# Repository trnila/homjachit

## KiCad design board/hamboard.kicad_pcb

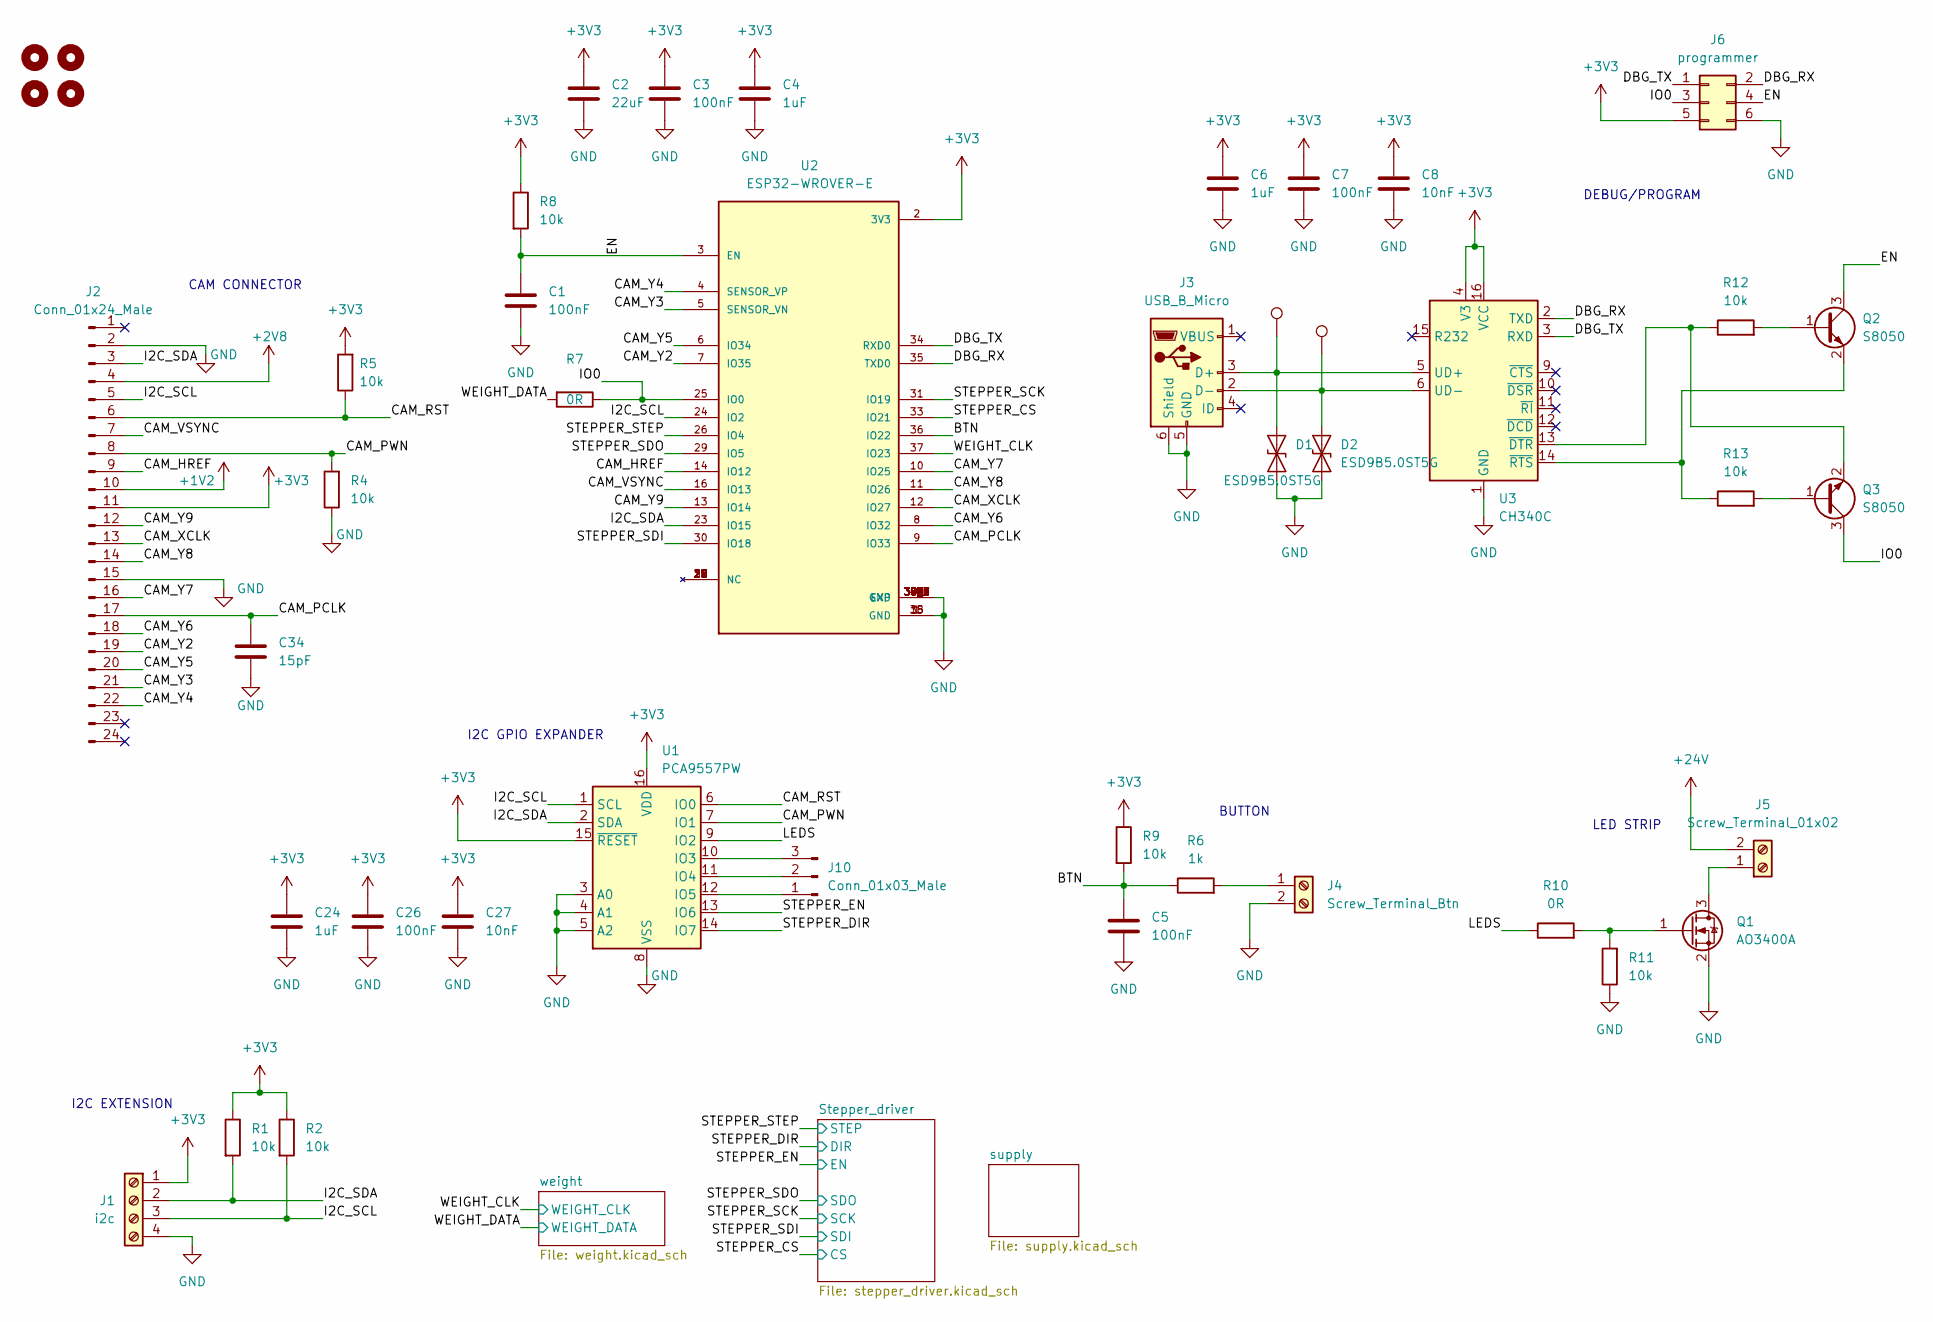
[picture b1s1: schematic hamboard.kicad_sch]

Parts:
C1, C3, C5, C7, C26: 100nF; C_0805_2012Metric; LCSC C282732
C2: 22uF; CP_EIA-1608-10_AVX-L; LCSC C29277
C4, C6, C24: 1uF; C_0805_2012Metric; LCSC C2798196
C8, C27: 10nF; C_0805_2012Metric; LCSC C376921
C34: 15pF; C_0805_2012Metric; LCSC C63339
D1, D2: ESD9B5.0ST5G; D_SOD-923; LCSC C2985641
H1, H2, H3, H4: MountingHole; MountingHole_3.2mm_M3
J1: i2c; PinHeader_1x04_P2.54mm_Vertical; LCSC C557656
J2: Conn_01x24_Male; Hirose_FH12-24S-0.5SH_1x24-1MP_P0.50mm_Horizontal; LCSC C2858298
J3: USB_B_Micro; USB_Micro-B_GCT_USB3076-30-A; LCSC C132562
J4: Screw_Terminal_Btn; TerminalBlock_bornier-2_P5.08mm; LCSC C394556
J5: Screw_Terminal_01x02; TerminalBlock_bornier-2_P5.08mm; LCSC C394556
J6: programmer; PinHeader_2x03_P2.54mm_Vertical
J10: Conn_01x03_Male; PinHeader_1x03_P2.54mm_Vertical
Q1: AO3400A; SOT-23; LCSC C347475
Q2, Q3: S8050; SOT-23; LCSC C2891804
R1, R2, R4, R5, R8, R9, R11, R12, R13: 10k; R_0805_2012Metric; LCSC C2930231
R6: 1k; R_0805_2012Metric; LCSC C2907295
R7: 0R; R_0805_2012Metric; LCSC C2930231
R10: 0R; R_0805_2012Metric; LCSC C2907288
TP10, TP11: TestPoint; TestPoint_Pad_D1.5mm
U1: PCA9557PW; TSSOP-16_4.4x5mm_P0.65mm; LCSC C141380
U2: ESP32-WROVER-E; XCVR_ESP32-WROVER-E-N4R8; PARTREV 1.6; LCSC C529589
U3: CH340C; SOIC-16_3.9x9.9mm_P1.27mm; LCSC C84681

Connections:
+1V2: J2.10; also elsewhere on the board
+2V8: J2.4; also elsewhere on the board
+3V3: C2.1, C3.1, C4.1, C6.1, C7.1, C8.1, C24.1, C26.1, C27.1, J1.1, J2.11, J6.5, R1.1, R2.1, R5.2, R8.1, R9.1, U1.15 (~RESET), U1.16 (VDD), U2.2 (3V3), U3.4 (V3), U3.16 (VCC); also elsewhere on the board
+24V: J5.2; also elsewhere on the board
/BTN: C5.1, R6.1, R9.2, U2.36 (IO22)
/CAM_HREF: J2.9, U2.14 (IO12)
/CAM_PCLK: C34.1, J2.17, U2.9 (IO33)
/CAM_PWN: J2.8, R4.2, U1.7 (IO1)
/CAM_RST: J2.6, R5.1, U1.6 (IO0)
/CAM_VSYNC: J2.7, U2.16 (IO13)
/CAM_XCLK: J2.13, U2.12 (IO27)
/CAM_Y2: J2.19, U2.7 (IO35)
/CAM_Y3: J2.21, U2.5 (SENSOR_VN)
/CAM_Y4: J2.22, U2.4 (SENSOR_VP)
/CAM_Y5: J2.20, U2.6 (IO34)
/CAM_Y6: J2.18, U2.8 (IO32)
/CAM_Y7: J2.16, U2.10 (IO25)
/CAM_Y8: J2.14, U2.11 (IO26)
/CAM_Y9: J2.12, U2.13 (IO14)
/DBG_RX: J6.2, U2.35 (TXD0), U3.2 (TXD)
/DBG_TX: J6.1, U2.34 (RXD0), U3.3 (RXD)
/EN: C1.1, J6.4, Q2.3 (C), R8.2, U2.3 (EN)
/I2C_SCL: J1.3, J2.5, R2.2, U1.1 (SCL), U2.24 (IO2)
/I2C_SDA: J1.2, J2.3, R1.2, U1.2 (SDA), U2.23 (IO15)
/IO0: J6.3, Q3.3 (C), R7.1, U2.25 (IO0)
/LEDS: R10.1, U1.9 (IO2)
/STEPPER_CS: U2.33 (IO21); also elsewhere on the board
/STEPPER_DIR: U1.14 (IO7); also elsewhere on the board
/STEPPER_EN: U1.13 (IO6); also elsewhere on the board
/STEPPER_SCK: U2.31 (IO19); also elsewhere on the board
/STEPPER_SDI: U2.30 (IO18); also elsewhere on the board
/STEPPER_SDO: U2.29 (IO5); also elsewhere on the board
/STEPPER_STEP: U2.26 (IO4); also elsewhere on the board
/WEIGHT_CLK: U2.37 (IO23); also elsewhere on the board
/WEIGHT_DATA: R7.2; also elsewhere on the board
GND: C1.2, C2.2, C3.2, C4.2, C5.2, C6.2, C7.2, C8.2, C24.2, C26.2, C27.2, C34.2, D1.1 (A1), D2.1 (A1), J1.4, J2.2, J2.15, J3.5 (GND), J3.6 (Shield), J4.2, J6.6, Q1.2 (S), R4.1, R11.1, U1.3 (A0), U1.4 (A1), U1.5 (A2), U1.8 (VSS), U2.1 (GND), U2.15 (GND), U2.38 (GND), U2.39_1 (EXP), U2.39_2 (EXP), U2.39_3 (EXP), U2.39_4 (EXP), U2.39_5 (EXP), U2.39_6 (EXP), U2.39_7 (EXP), U2.39_8 (EXP), U2.39_9 (EXP), U2.40 (GND), U2.41 (GND), U2.42 (GND), U2.43 (GND), U2.44 (GND), U2.45 (GND), U2.46 (GND), U2.47 (GND), U2.48 (GND), U2.49 (GND), U2.50 (GND), U2.51 (GND), U3.1 (GND); also elsewhere on the board
unnamed: D1.2 (A2), J3.3 (D+), TP10.1, U3.5 (UD+)
unnamed: D2.2 (A2), J3.2 (D-), TP11.1, U3.6 (UD-)
unnamed: J4.1, R6.2
unnamed: J5.1, Q1.3 (D)
unnamed: J10.1, U1.12 (IO5)
unnamed: J10.2, U1.11 (IO4)
unnamed: J10.3, U1.10 (IO3)
unnamed: Q1.1 (G), R10.2, R11.2
unnamed: Q2.1 (B), R12.2
unnamed: Q2.2 (E), R13.1, U3.14 (~RTS)
unnamed: Q3.1 (B), R13.2
unnamed: Q3.2 (E), R12.1, U3.13 (~DTR)

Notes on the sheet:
I2C GPIO EXPANDER
CAM CONNECTOR
DEBUG/PROGRAM
BUTTON
I2C EXTENSION
LED STRIP

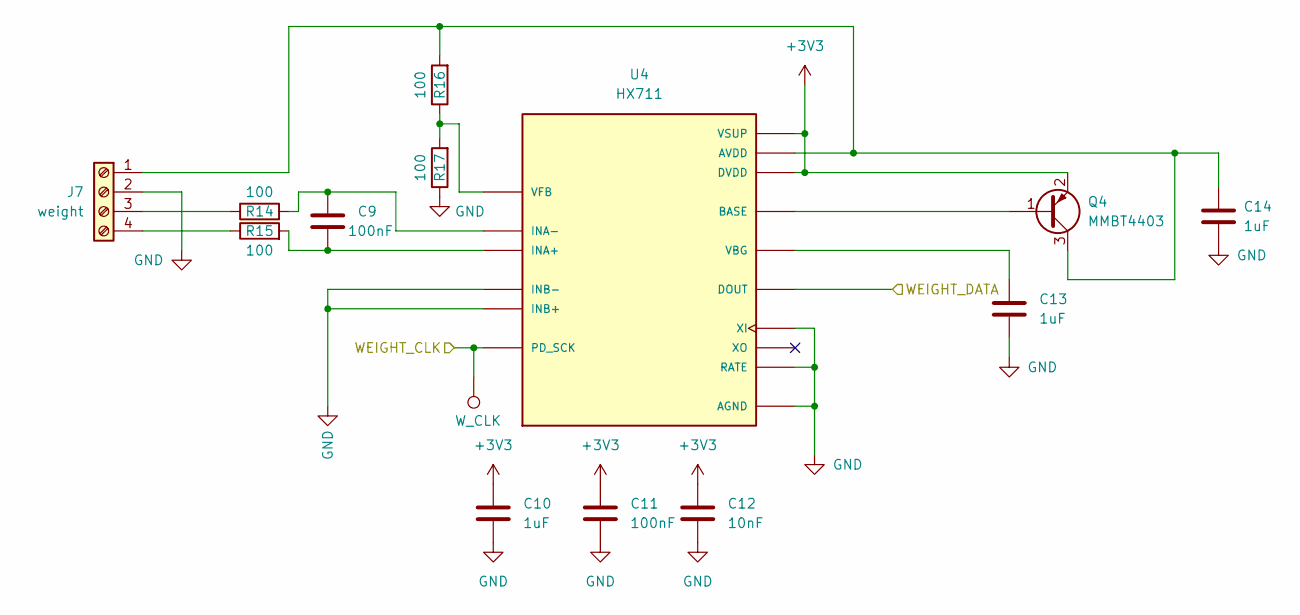
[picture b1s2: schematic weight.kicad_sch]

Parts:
C9, C11: 100nF; C_0805_2012Metric
C10, C13, C14: 1uF; C_0805_2012Metric
C12: 10nF; C_0805_2012Metric
J7: weight; TerminalBlock_bornier-4_P5.08mm; LCSC C557656
Q4: MMBT4403; SOT-23; LCSC C181124
R14, R15, R16, R17: 100; R_0805_2012Metric
TP4: W_CLK; TestPoint_Pad_D1.5mm
U4: HX711; SOP127P600X180-16N; PARTREV V2.0; LCSC C43656

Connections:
+3V3: C10.1, C11.1, C12.1, Q4.2 (E), U4.1 (VSUP), U4.16 (DVDD); also elsewhere on the board
/WEIGHT_CLK: TP4.1, U4.11 (PD_SCK); also elsewhere on the board
/WEIGHT_DATA: U4.12 (DOUT); also elsewhere on the board
GND: C10.2, C11.2, C12.2, C13.2, C14.2, J7.2, R17.1, U4.5 (AGND), U4.9 (INB-), U4.10 (INB+), U4.14 (XI), U4.15 (RATE); also elsewhere on the board
unnamed: C9.1, R14.2, U4.7 (INA-)
unnamed: C9.2, R15.2, U4.8 (INA+)
unnamed: C13.1, U4.6 (VBG)
unnamed: C14.1, J7.1, Q4.3 (C), R16.2, U4.3 (AVDD)
unnamed: J7.3, R14.1
unnamed: J7.4, R15.1
unnamed: Q4.1 (B), U4.2 (BASE)
unnamed: R16.1, R17.2, U4.4 (VFB)

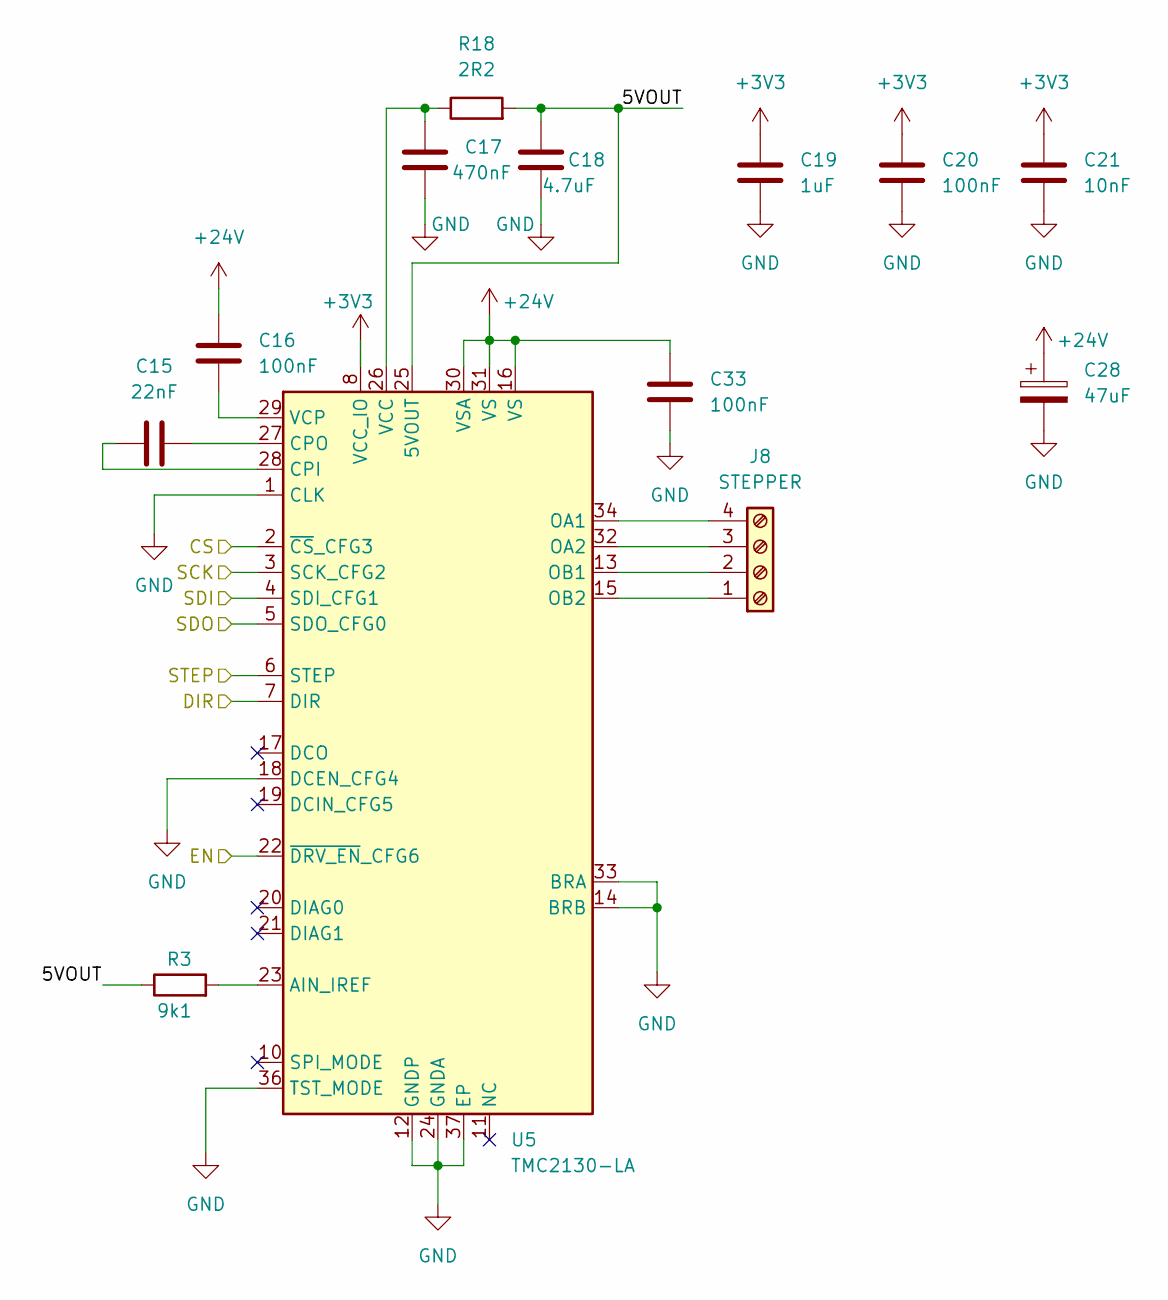
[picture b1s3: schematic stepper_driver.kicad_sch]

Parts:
C15: 22nF; C_0805_2012Metric
C16, C20, C33: 100nF; C_0805_2012Metric
C17: 470nF; C_0805_2012Metric
C18: 4.7uF; C_0805_2012Metric
C19: 1uF; C_0805_2012Metric
C21: 10nF; C_0805_2012Metric
C28: 47uF; CP_Elec_6.3x7.7; LCSC C88677
J8: STEPPER; TerminalBlock_bornier-4_P5.08mm; LCSC C557656
R3: 9k1; R_0805_2012Metric
R18: 2R2; R_0805_2012Metric
U5: TMC2130-LA; QFN-36-1EP_5x6mm_P0.5mm_EP3.6x4.1mm; LCSC C915795

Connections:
+3V3: C19.1, C20.1, C21.1, U5.8 (VCC_IO); also elsewhere on the board
+24V: C16.2, C28.1, C33.1, U5.16 (VS), U5.30 (VSA), U5.31 (VS); also elsewhere on the board
/STEPPER_CS: U5.2 (~CS_CFG3); also elsewhere on the board
/STEPPER_DIR: U5.7 (DIR); also elsewhere on the board
/STEPPER_EN: U5.22 (~DRV_EN_CFG6); also elsewhere on the board
/STEPPER_SCK: U5.3 (SCK_CFG2); also elsewhere on the board
/STEPPER_SDI: U5.4 (SDI_CFG1); also elsewhere on the board
/STEPPER_SDO: U5.5 (SDO_CFG0); also elsewhere on the board
/STEPPER_STEP: U5.6 (STEP); also elsewhere on the board
/Stepper_driver/5VOUT: C18.1, R3.1, R18.2, U5.25 (5VOUT)
GND: C17.2, C18.2, C19.2, C20.2, C21.2, C28.2, C33.2, U5.1 (CLK), U5.12 (GNDP), U5.14 (BRB), U5.18 (DCEN_CFG4), U5.24 (GNDA), U5.33 (BRA), U5.35 (GNDP), U5.36 (TST_MODE), U5.37 (EP); also elsewhere on the board
unnamed: C15.1, U5.28 (CPI)
unnamed: C15.2, U5.27 (CPO)
unnamed: C16.1, U5.29 (VCP)
unnamed: C17.1, R18.1, U5.26 (VCC)
unnamed: J8.1, U5.15 (OB2)
unnamed: J8.2, U5.13 (OB1)
unnamed: J8.3, U5.32 (OA2)
unnamed: J8.4, U5.34 (OA1)
unnamed: R3.2, U5.23 (AIN_IREF)

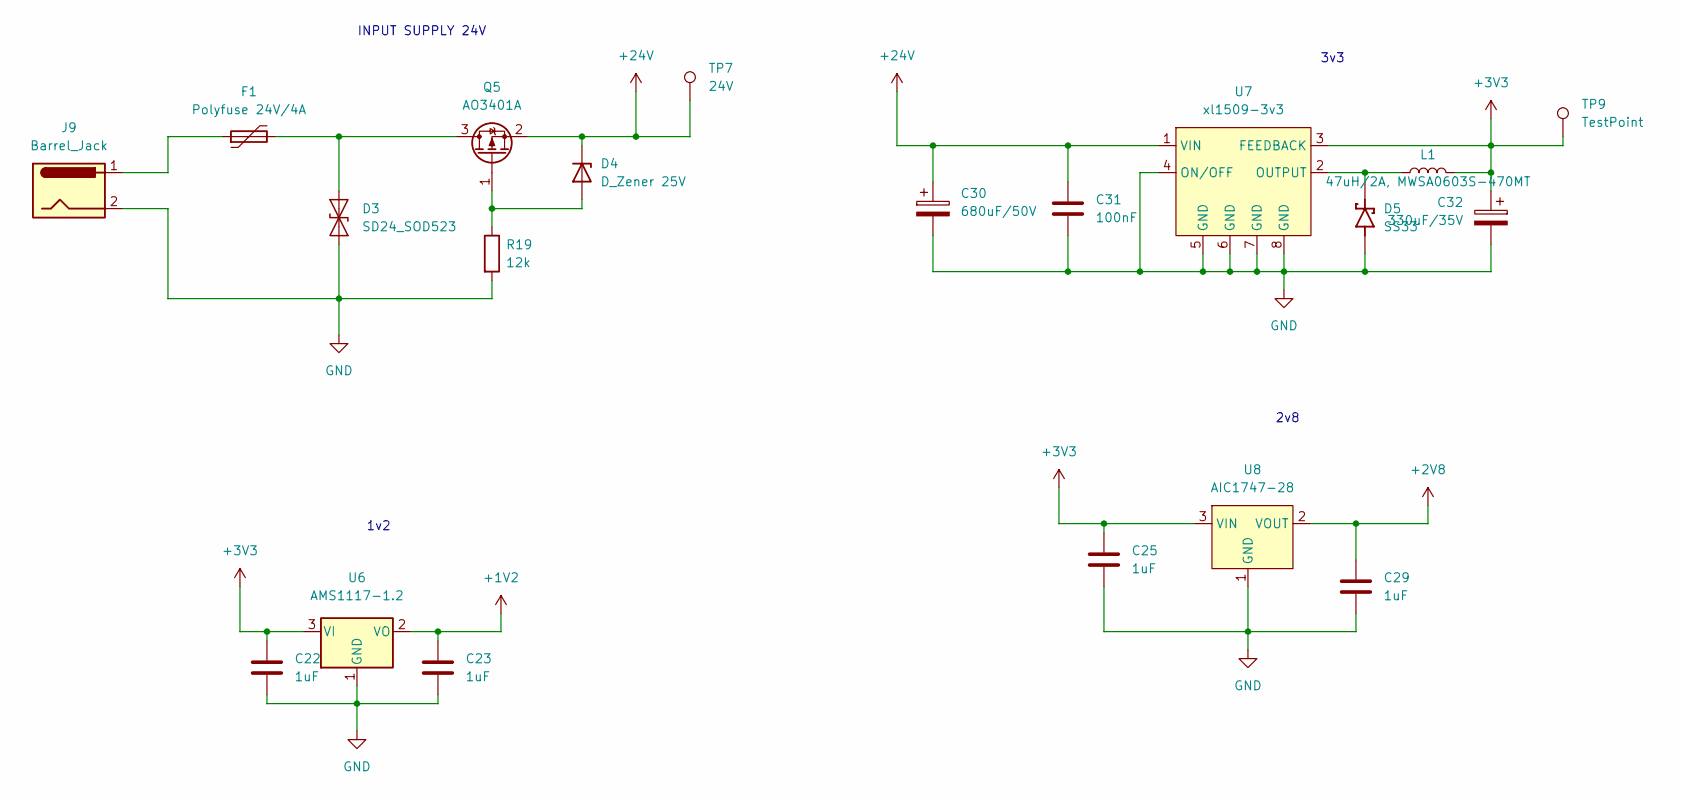
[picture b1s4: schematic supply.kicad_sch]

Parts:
C22, C23, C25, C29: 1uF; C_0805_2012Metric
C30: 680uF/50V; CP_Radial_D13.0mm_P5.00mm; LCSC C399014
C31: 100nF; C_0805_2012Metric
C32: 330uF/35V; CP_Elec_10x10.5; LCSC C310832
D3: SD24_SOD523; D_SOD-323; LCSC C558432
D4: D_Zener 25V; D_MiniMELF; LCSC C118705
D5: SS33; DIOM6859X262N; PARTREV Q2102; LCSC C64998
F1: Polyfuse 24V/4A; Fuse_2920_7451Metric; LCSC C2982292
J9: Barrel_Jack; BarrelJack_CLIFF_FC681465S_SMT_Horizontal; LCSC C381116
L1: 47uH/2A, MWSA0603S-470MT; L_7.3x7.3_H3.5; LCSC C408455
Q5: AO3401A; SOT-23; LCSC C700954
R19: 12k; R_0805_2012Metric
TP7: 24V; TestPoint_Pad_D1.5mm
TP9: TestPoint; TestPoint_Pad_D1.5mm
U6: AMS1117-1.2; SOT-223-3_TabPin2; LCSC C2992568
U7: xl1509-3v3; SOIC-8_3.9x4.9mm_P1.27mm; LCSC C2681226
U8: AIC1747-28; TSOT-23_HandSoldering; LCSC C238238

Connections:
+1V2: C23.1, U6.2 (VO); also elsewhere on the board
+2V8: C29.1, U8.2 (VOUT); also elsewhere on the board
+3V3: C22.1, C25.1, C32.1, L1.2, TP9.1, U6.3 (VI), U7.3 (FEEDBACK), U8.3 (VIN); also elsewhere on the board
+24V: C30.1, C31.1, D4.1 (K), Q5.2 (S), TP7.1, U7.1 (VIN); also elsewhere on the board
GND: C22.2, C23.2, C25.2, C29.2, C30.2, C31.2, C32.2, D3.1 (A1), D5.A, J9.2, R19.2, U6.1 (GND), U7.4 (ON/OFF), U7.5 (GND), U7.6 (GND), U7.7 (GND), U7.8 (GND), U8.1 (GND); also elsewhere on the board
unnamed: D3.2 (A2), F1.2, Q5.3 (D)
unnamed: D4.2 (A), Q5.1 (G), R19.1
unnamed: D5.C, L1.1, U7.2 (OUTPUT)
unnamed: F1.1, J9.1

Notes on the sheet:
1v2
2v8
3v3
INPUT SUPPLY 24V

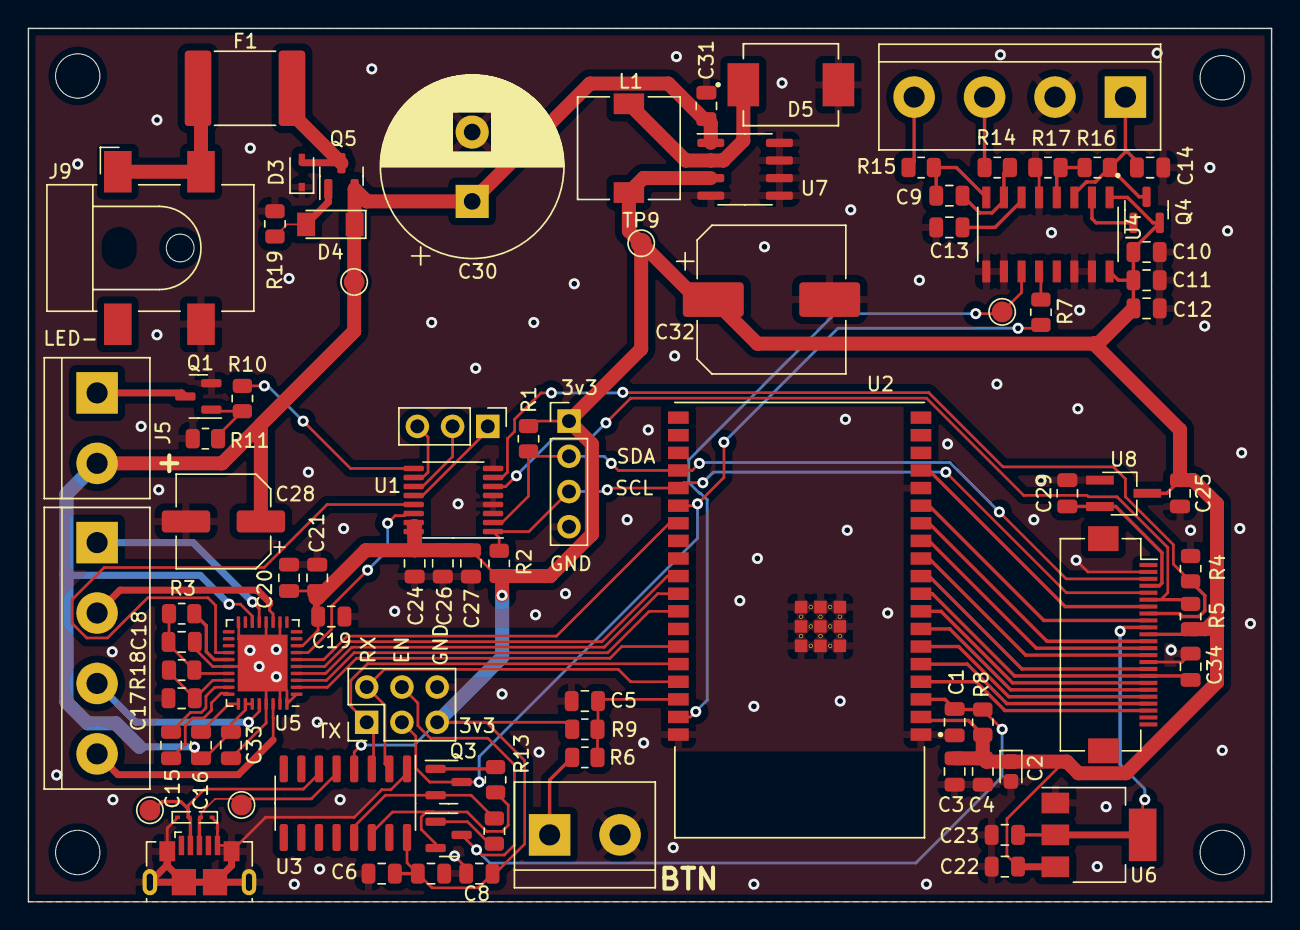
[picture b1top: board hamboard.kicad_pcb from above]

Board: 2 copper layers, 89.7 x 63.0 mm, 92 parts (0 on the bottom side), 70 nets.

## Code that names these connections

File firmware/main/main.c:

#include <esp_log.h>
#include <nvs_flash.h>
#include "esp_wifi.h"
#include "esp_http_server.h"
#include "camera.h"
#include "stream.h"
#include "driver/gpio.h"
#include "driver/i2c.h"
#include "driver/spi_master.h"
#include <driver/mcpwm.h>




esp_err_t httpd_get_index(httpd_req_t *req){
  httpd_resp_sendstr(req, "<h1>oVerEnginEEred automatic feeder</h1><img id='camera'><img id='camera'><script>document.getElementById('camera').src = `http://${document.location.host}:81/`;</script>");
  return ESP_OK;
}

httpd_uri_t uri_get = {
  .uri      = "/",
  .method   = HTTP_GET,
  .handler  = httpd_get_index,
  .user_ctx = NULL
};

static char stats[1024];

#define LED_PIN 21
#define BTN_PIN 22
#define STEP_PIN 4
#define IO_SPI_CS 5
#define IO_STEPPER_DIR 6
#define IO_STEPPER_EN 7
int i2c_master_port = 0;
uint8_t pins_state = 0;


void set_pin(uint8_t pin, bool state) {
  if(state) {
    pins_state |= 1U << pin;
  } else {
    pins_state &= ~(1U << pin);
  }

  uint8_t write_buf[] = {0x01, pins_state};
  ESP_ERROR_CHECK(i2c_master_write_to_device(i2c_master_port, 0x18, write_buf, sizeof(write_buf), 1000 / portTICK_PERIOD_MS));
}

static void cs_high(spi_transaction_t* t) {
  set_pin(IO_SPI_CS, 0);
}

static void cs_low(spi_transaction_t* t) {
  set_pin(IO_SPI_CS, 1);
}

void motor_read(spi_device_handle_t spi_handle, uint8_t reg) {
    uint8_t tx[5] = {
      reg,
    };
    uint8_t rx[5] = {};
    spi_transaction_t t = {};
    t.length = 40;
    t.tx_buffer = tx;
    t.rx_buffer = rx;
    ESP_ERROR_CHECK(spi_device_polling_transmit(spi_handle, &t));
    ESP_ERROR_CHECK(spi_device_polling_transmit(spi_handle, &t));

    ESP_LOG_BUFFER_HEXDUMP("spi", rx, sizeof(rx), ESP_LOG_ERROR);
}

void motor_write(spi_device_handle_t spi_handle, uint8_t reg, uint32_t data) {
    uint8_t tx[5] = {
      reg | (1U << 7U),
      (data >> 24) & 0xFFU,
      (data >> 16) & 0xFFU,
      (data >> 8) & 0xFFU,
      (data) & 0xFFU,
    };

    ESP_LOG_BUFFER_HEXDUMP("spitx", tx, sizeof(tx), ESP_LOG_ERROR);

    uint8_t rx[5] = {};
    spi_transaction_t t = {};
    t.length = 40;
    t.tx_buffer = tx;
    t.rx_buffer = rx;
    ESP_ERROR_CHECK(spi_device_polling_transmit(spi_handle, &t));

    ESP_LOG_BUFFER_HEXDUMP("spirx", rx, sizeof(rx), ESP_LOG_ERROR);
}

void motor_writeraw(spi_device_handle_t spi_handle, uint64_t data) {
    uint8_t tx[5] = {
      (data >> 32) & 0xFFU,
      (data >> 24) & 0xFFU,
      (data >> 16) & 0xFFU,
      (data >> 8) & 0xFFU,
      (data) & 0xFFU,
    };

    ESP_LOG_BUFFER_HEXDUMP("spitx", tx, sizeof(tx), ESP_LOG_ERROR);

    uint8_t rx[5] = {};
    spi_transaction_t t = {};
    t.length = 40;
    t.tx_buffer = tx;
    t.rx_buffer = rx;
    ESP_ERROR_CHECK(spi_device_polling_transmit(spi_handle, &t));

    ESP_LOG_BUFFER_HEXDUMP("spirx", rx, sizeof(rx), ESP_LOG_ERROR);
}

static void IRAM_ATTR weight_ready_isr_handler(void* arg) {  
  ESP_LOGE("x", "ISR\n");
}

void app_main() {
  gpio_config_t gpio_led = {};
  gpio_led.mode = GPIO_MODE_OUTPUT;
  gpio_led.pin_bit_mask = 1ULL << LED_PIN;
  ESP_ERROR_CHECK(gpio_config(&gpio_led));

  memset(&gpio_led, 0, sizeof(gpio_led));
  gpio_led.mode = GPIO_MODE_INPUT;
  gpio_led.pin_bit_mask = 1ULL << BTN_PIN;
  ESP_ERROR_CHECK(gpio_config(&gpio_led));


  i2c_config_t conf = {
    .mode = I2C_MODE_MASTER,
    .sda_io_num = 15,
    .sda_pullup_en = GPIO_PULLUP_ENABLE,
    .scl_io_num = 2,
    .scl_pullup_en = GPIO_PULLUP_ENABLE,
    .master.clk_speed = 100000,
    .clk_flags = 0,
  };
  ESP_ERROR_CHECK(i2c_param_config(i2c_master_port, &conf));
  ESP_ERROR_CHECK(i2c_driver_install(i2c_master_port, conf.mode, 0, 0, 0));


  spi_bus_config_t buscfgw={
    .miso_io_num = 0,
    .mosi_io_num = -1,
    .sclk_io_num = 23,
    .quadwp_io_num = -1,
    .quadhd_io_num = -1,
    .max_transfer_sz = 4,
  };

  esp_err_t ret = spi_bus_initialize(SPI3_HOST, &buscfgw, SPI_DMA_DISABLED);
  ESP_ERROR_CHECK(ret);

  spi_device_interface_config_t confw = {
      .mode = 1,
      .clock_speed_hz = 500000,
      .spics_io_num = -1,
      .queue_size = 1,
  };

  spi_device_handle_t weight_spi_dev;
  ret = spi_bus_add_device(SPI3_HOST, &confw, &weight_spi_dev);
  ESP_ERROR_CHECK(ret);

   gpio_config_t io_conf;
    io_conf.mode = GPIO_MODE_INPUT;
    io_conf.pin_bit_mask = 1ULL << 0;
    io_conf.intr_type = GPIO_INTR_NEGEDGE;
    io_conf.pull_down_en = false;
    io_conf.pull_up_en = false;
    ret = gpio_config(&io_conf);
    assert(ret == ESP_OK);

    gpio_isr_handler_add(0, weight_ready_isr_handler,NULL);


  // set all pins to output
  uint8_t write_buf[] = {0x03, 0x00};
  ESP_ERROR_CHECK(i2c_master_write_to_device(i2c_master_port, 0x18, write_buf, sizeof(write_buf), 1000 / portTICK_PERIOD_MS));

  spi_bus_config_t buscfg={
    .miso_io_num = 5,
    .mosi_io_num = 18,
    .sclk_io_num = 19,
    .quadwp_io_num = -1,
    .quadhd_io_num = -1,
    .max_transfer_sz = 40,
  };
  ESP_ERROR_CHECK(spi_bus_initialize(SPI2_HOST, &buscfg, SPI_DMA_CH_AUTO));

  spi_device_handle_t spi_handle;
  spi_device_interface_config_t devcfg={
    .command_bits = 0,
    .clock_speed_hz = 100000,
    .mode = 3,
    .spics_io_num = -1,
    .queue_size = 1,
    .flags = SPI_DEVICE_POSITIVE_CS,
    .pre_cb = cs_high,
    .post_cb = cs_low,
    .input_delay_ns = 100,
  };
  ESP_ERROR_CHECK(spi_bus_add_device(SPI2_HOST, &devcfg, &spi_handle));

  set_pin(IO_STEPPER_DIR, 0);
  set_pin(IO_STEPPER_EN, 1);

  memset(&gpio_led, 0, sizeof(gpio_led));
  gpio_led.mode = GPIO_MODE_OUTPUT;
  gpio_led.pin_bit_mask = 1ULL << STEP_PIN;
  ESP_ERROR_CHECK(gpio_config(&gpio_led));

//  motor_write(spi_handle, 0x00, (1U << 1U));

  //motor_write(spi_handle, 0x6c, 4);

  /*
  motor_write(spi_handle, 0x10, (20) | (31<<8) | (1 << 16));
  motor_write(spi_handle, 0x11, 127);


  // chopper
  motor_write(spi_handle, 0x00, (1U << 1U) | (1U << 2U));

  motor_write(spi_handle, 0x70, (1U << 18U) | (1U << 8U) | (255));

  motor_write(spi_handle, 0x6c, 4 | (2 << 15) | (4 << 4));

  motor_write(spi_handle, 0x13, 500);
  */

  motor_writeraw(spi_handle, 0xEC000100C3);
  motor_writeraw(spi_handle, 0x9000061F0A);
  motor_writeraw(spi_handle, 0x910000000A);
  motor_writeraw(spi_handle, 0x8000000004 | (1 << 1));
  motor_writeraw(spi_handle, 0x93000001F4);
  motor_writeraw(spi_handle, 0xF0000401C8);

   
  mcpwm_gpio_init(MCPWM_UNIT_0, MCPWM0A, STEP_PIN);

  // Configure the PWM signal parameters
  mcpwm_config_t pwm_config;
  pwm_config.frequency = 50000;  // Set the frequency to 100kHz
  pwm_config.cmpr_a = 50.0;       // Set the duty cycle to 50%
  pwm_config.counter_mode = MCPWM_UP_COUNTER;
  pwm_config.duty_mode = MCPWM_DUTY_MODE_0;

  // Set the configuration
  mcpwm_init(MCPWM_UNIT_0, MCPWM_TIMER_0, &pwm_config);



  set_pin(IO_STEPPER_EN, 0);

  int i = 0;
  bool led_state = false; 
  for(;;) {
  //  ESP_LOGI("test", "cus kaktus %d %d", i++, gpio_get_level(BTN_PIN));
    //gpio_set_level(LED_PIN, led_state);
    //led_state = !led_state;

    //uint8_t write_buf[] = {0x01, led_state ? 0xFF : 0x00};
    //ESP_ERROR_CHECK(i2c_master_write_to_device(i2c_master_port, 0x18, write_buf, sizeof(write_buf), 1000 / portTICK_PERIOD_MS));
    
    //set_pin(2, led_state);

    //esp_rom_delay_us(100);

    //gpio_set_level(STEP_PIN, led_state);
/*
    motor_read(spi_handle, 0x01);
    motor_read(spi_handle, 0x6F);
    motor_read(spi_handle, 0x04);
    ESP_LOGE("TAG", "\n\n");


    vTaskDelay(10);*/

    int clk_bits = 25;
    spi_transaction_t t = {
        .flags = SPI_TRANS_USE_RXDATA,
        .length = clk_bits,
        .rxlength = clk_bits,
    };

    spi_device_transmit(weight_spi_dev, &t);

    uint32_t measurement = SPI_SWAP_DATA_RX(*(uint32_t*)t.rx_data, clk_bits - 1);
    // fix 2's complement
    //if(measurement & (1 << 23)) {
        //measurement |= 0xFF000000;
    //}

    ESP_LOGE("TAG", "%x", measurement);

    vTaskDelay(50);
  }

  nvs_flash_init();

  ESP_ERROR_CHECK(esp_netif_init());
  ESP_ERROR_CHECK(esp_event_loop_create_default());
  esp_netif_create_default_wifi_sta();

  wifi_init_config_t cfg = WIFI_INIT_CONFIG_DEFAULT();
  ESP_ERROR_CHECK(esp_wifi_init(&cfg));

  wifi_config_t wifi_config = {
    .sta = {
      .ssid = "user",
      .password = "pass",
    },
  };
  ESP_ERROR_CHECK(esp_wifi_set_mode(WIFI_MODE_STA));
  ESP_ERROR_CHECK(esp_wifi_set_config(WIFI_IF_STA, &wifi_config));
  ESP_ERROR_CHECK(esp_wifi_start());
  ESP_ERROR_CHECK(esp_wifi_connect());

  ESP_ERROR_CHECK(camera_start());
  ESP_ERROR_CHECK(stream_start());

  httpd_config_t config = HTTPD_DEFAULT_CONFIG();
  httpd_handle_t server = NULL;
  if (httpd_start(&server, &config) == ESP_OK) {
    httpd_register_uri_handler(server, &uri_get);
  }

  for(;;) {
    vTaskGetRunTimeStats(stats);
    printf("%s\n", stats);
    vTaskDelay(1000);
  }
}

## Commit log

2022-07-05 Dedicated server for streaming
2022-07-05 distribute to all clients
2022-07-05 prevent slow client to slow everyone
2022-07-05 handle subscription by camera task
2022-07-05 split to multiple files
2022-07-05 cleaned up code
2022-07-05 index: point to image stream
2022-08-24 initial board commit
2022-09-01 board: bom
2022-09-01 added libs
2022-09-07 first pcb layout
2022-09-10 pcb: added screws and rerouted everything
2022-09-10 board: correct DRC issues
2022-09-10 board: fixed esp heat pads
2022-09-10 Removed duplicated footprints
2022-09-10 pcb: Centered
2022-09-10 board: renamed directory
2023-02-25 some testing
2023-02-25 broken
2023-03-05 using motor pwm
2023-03-20 weight testing
